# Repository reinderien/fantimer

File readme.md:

# Fan Timer

## Directory

- `bom.fods` - Bill of materials
- `elsel.py` - Component selection and analysis script
- `eagle/` - Electrical schematic including design + engineering notes on hardware; wiring diagram
- `pic/` - Microcontroller source code
- `qucs/` - Some simulations, mostly of opto detector
- `report/` - TeX source and images for the report
- `specsheets/` - All associated specsheets (gitignored)

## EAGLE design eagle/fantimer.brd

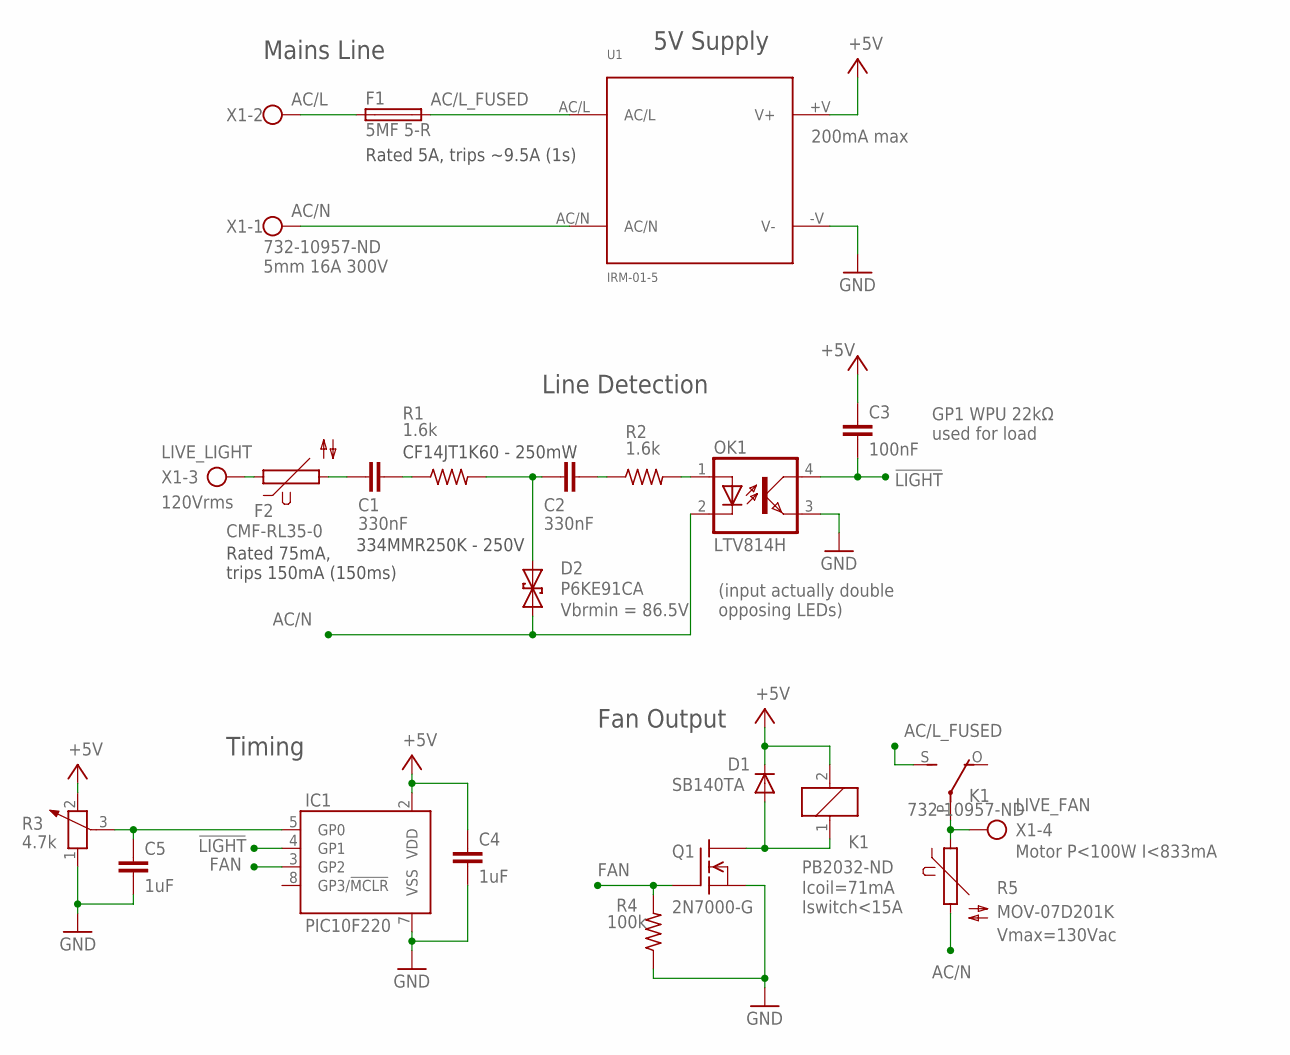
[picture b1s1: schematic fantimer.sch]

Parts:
C1, C2: 330nF; C102-064X133
C3: 100nF; C025-025X050
C4, C5: 1uF; C025-025X050
D1: SB140TA; DO41-7.6
D2: P6KE91CA; CB417-15
F1: 5MF 5-R; SHK20Q
F2: CMF-RL35-0; S05K11
IC1: PIC10F220; DIL08
K1: PB2032-ND; G5LE
OK1: LTV814H; DIL04
Q1: 2N7000-G; TO237
R1, R2: 1.6k; 0207/7
R3: 4.7k; PT-10
R4: 100k; 0207/7
R5: MOV-07D201K; S05K11
U1: IRM-01-5; IRM-01-X
X1: 732-10957-ND; W237-4

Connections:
!LIGHT: C3.2, IC1.4 (GP1), OK1.4 (COL)
+5V: C3.1, C4.1, D1.C, IC1.2 (VDD), K1.2, R3.2, U1.+V (V+)
AC/L: F1.1A (1), X1.2
AC/L_FUSED: F1.2A (2), K1.S, U1.AC/L
AC/N: D2.A (1), OK1.2 (C), R5.2, U1.AC/N, X1.1
ADJ: C5.1, IC1.5 (GP0), R3.3
COILOUT: D1.A, K1.1, Q1.1 (D)
DETECT_IN: OK1.1 (A), R2.2
FAN: IC1.3 (GP2), Q1.2 (G), R4.2
GND: C4.2, C5.2, IC1.7 (VSS), OK1.3 (EMIT), Q1.3 (S), R3.1, R4.1, U1.-V (V-)
LIVE_FAN: K1.P, R5.1, X1.4
LIVE_LIGHT: F2.1, X1.3
LIVE_LIGHT_FUSED: C1.1, F2.2
VRC1: C1.2, R1.1
VRC2: C2.2, R2.1
VZ: C2.1, D2.C (2), R1.2

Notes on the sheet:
732-10957-ND 5mm 16A 300V
200mA max
Motor P<100W I<833mA
Icoil=71mA Iswitch<15A
(input actually double opposing LEDs)
120Vrms
Vbrmin = 86.5V
GP1 WPU 22kΩ used for load
CF14JT1K60‎ - 250mW
334MMR250K‎ - 250V
5V Supply
Line Detection
Fan Output
Timing
Vmax=130Vac
Rated 5A, trips ~9.5A (1s)
Rated 75mA, trips 150mA (150ms)
Mains Line

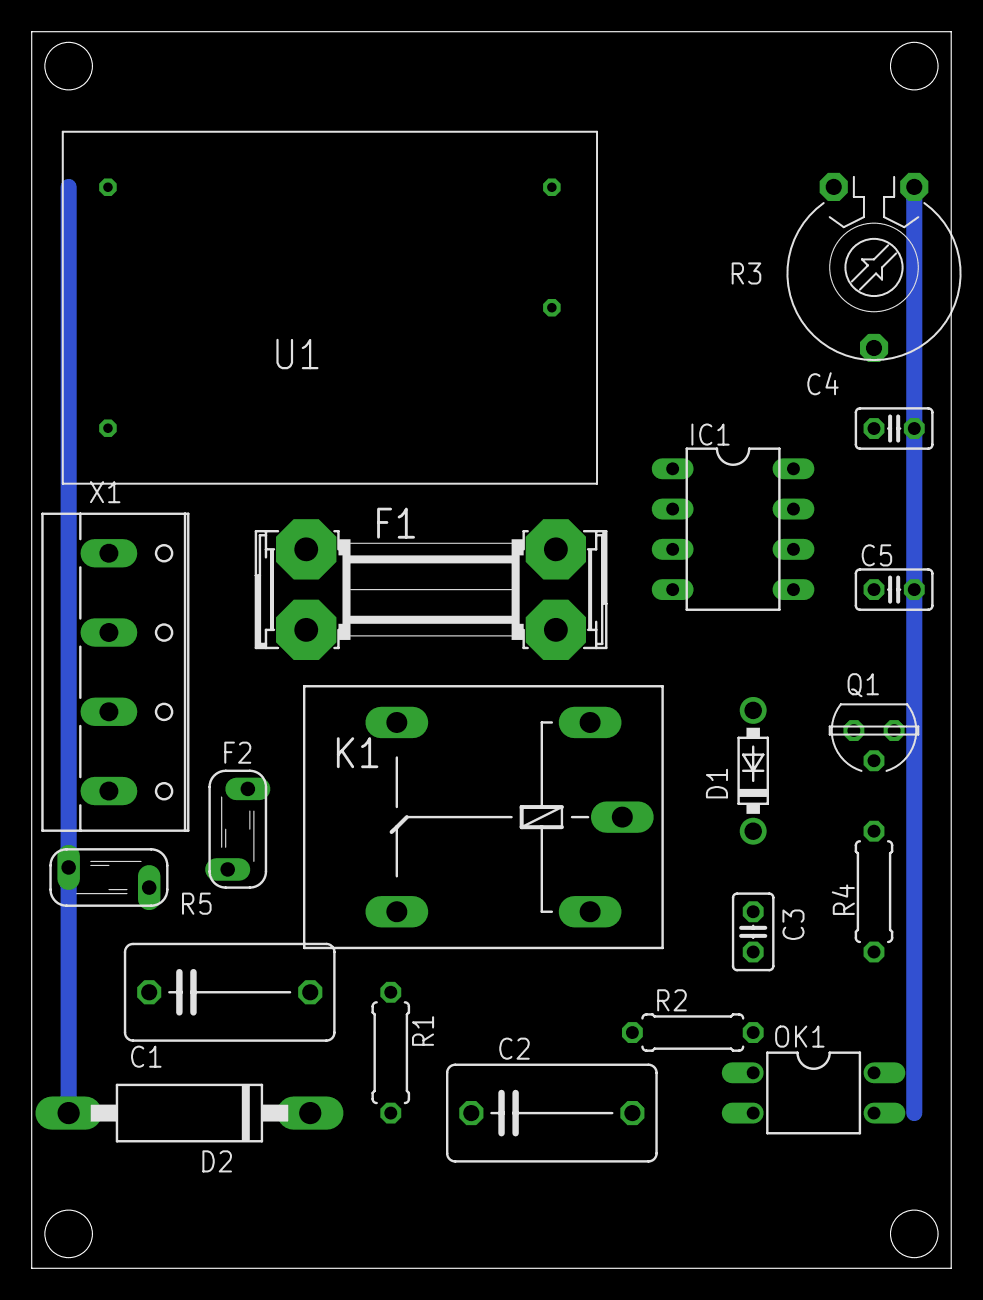
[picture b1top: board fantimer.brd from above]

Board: 2 copper layers, 58.0 x 78.0 mm, 20 parts (0 on the bottom side), 16 nets.

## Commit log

2018-09-24 First commit - output working
2018-09-24 Fix ImVz bug
2018-09-25 Caps are crappy, downgrade to E12. Reject rows with out-of-tol Vz.
2018-09-25 Sort by cost
2018-09-27 Replace cost col with cap voltages; only show equal RC with Vz at midpoint
2018-09-27 Consolidate pcb, sim and analysis
2018-09-27 BOM; start to a readme
2018-09-27 Renumber IC3 to IC1
2018-09-27 Timer board is not grounded
2018-09-27 Skeleton PIC project
2018-09-27 Move PIC project into a sane folder
2018-09-28 Split up prices into system and order; correct PIC part
2018-09-28 Ignore lock files
2018-09-28 Symlinks to device files for reference
2018-09-28 Drop some unnecessary asm
2018-09-28 Add ref files to project
2018-09-30 Add simulator
2018-09-30 Initial assembly. Add a better PIC Eagle lib. Remove PIC notes from sch.
2018-09-30 Add filter cap for MCU
2018-09-30 Some wire rearranging
2018-09-30 Pulldown 100k. Fix up diodes, resistors and filter cap in BOM.
2018-10-02 Replace TVS with varistor across relay
2018-10-02 Library updates
2018-10-02 Fix pullup info
2018-10-02 Fix incorrect op
2018-10-04 Adjust detection cap based on experiment
2018-10-04 logic level fixes for light
2018-10-05 Only modify OSCCAL on POR; port writes must occur after option/ADCON; three fixes for silly issues in timer loop
2018-10-06 Some files for simulation
2018-10-06 Fix comment
2018-10-07 More realistic input timings for sim
2018-10-07 Increase detection filter cap; add pot cap
2018-10-07 BOM - increase detection filter cap; add pot cap
2018-10-08 Wrap to 80-ish columns
2018-10-08 Start to report in TeX
2018-10-08 Fill out report to detector
2018-10-08 Notes on opto output
2018-10-08 Mention report in dir
2018-10-08 Place C5
2018-10-08 Upgrade Eagle to 9.2
2018-10-08 Scope graphs; opto output explanation
2018-10-08 Tweak some reference formats; temporarily get rid of ohm symbols in text body because fonts are broken; fix figure alignments
2018-10-08 Fix capital
2018-10-08 Timing and output sections
2018-10-08 Fix some alignment
2018-10-08 Automatic, not autonomous; study desc; opto subsections; opto off timing; Q1 desc; alignment fix
2018-10-09 Simulation notes and graphs
2018-10-09 Conclusion
2018-10-09 Workaround for PIC simulator voltage axis bug
2018-10-09 Fix reversed PSU
2018-10-09 - Fix for backward PSU - CPTC fuse added on light line - Filament fuse added on AC/L line - Drop analysis (that goes in the report)
2018-10-09 Clean up simulation for report
2018-10-09 Add fuses and fuse clips
2018-10-09 More citations. general editing. fuses added. hardware tools sect. empty BOM added.
2018-10-09 Fill out BOM. Tweak some graph widths.
2018-10-10 Add board section
2018-10-10 Clean up for report; add high-v line
2018-10-10 Newlines before links in references
2018-10-10 Wiring diagram
2018-10-10 Clean up for report
2018-10-13 Rearrange board taking advantage of ground buses. CPTC is narrower than predicted.
2018-10-13 Completion photo
2018-10-14 Move TVS closer to neut bus
2018-10-14 Split apart terminal pins to represent circuit logically. Swap terminal 3+4 for better routing. Drop intro text from asm. General report edits.
2018-10-14 Tweak sch for more compact print
2018-10-15 Back and forward quotes; mention trimmer leads
